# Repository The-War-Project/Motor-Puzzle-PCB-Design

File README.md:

# Motor-Puzzle-PCB-Design
 PCB Design in Kicad of the Motor Puzzle

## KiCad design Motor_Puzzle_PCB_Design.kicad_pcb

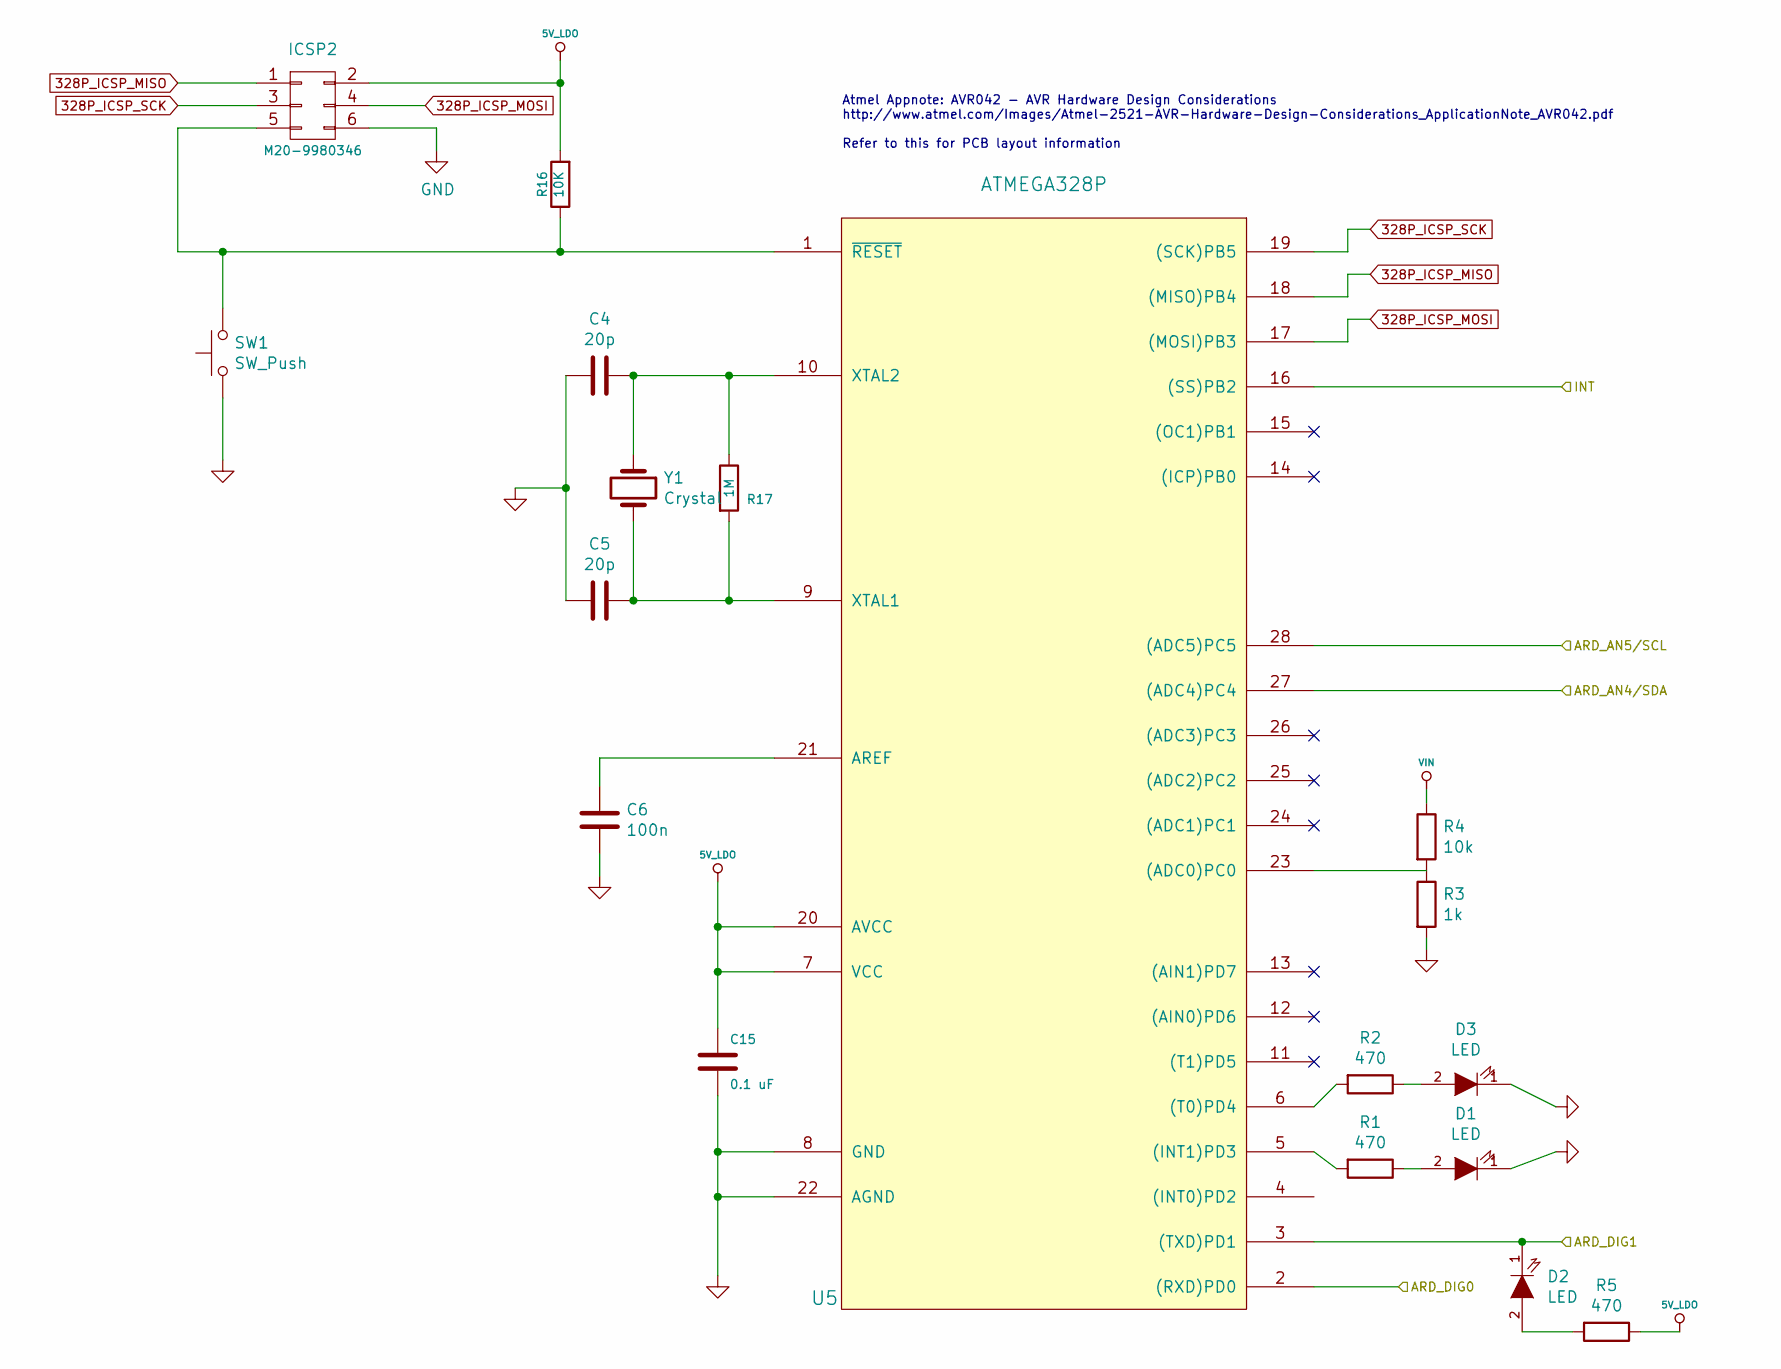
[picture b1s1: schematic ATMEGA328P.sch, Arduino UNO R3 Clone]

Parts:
C4, C5: 20p; C_0805_2012Metric_Pad1.15x1.40mm_HandSolder
C6: 100n; C_0805_2012Metric_Pad1.15x1.40mm_HandSolder
C15: 0.1 uF; C_0805_2012Metric_Pad1.15x1.40mm_HandSolder
D1, D2, D3: LED; LED_0805_2012Metric_Pad1.15x1.40mm_HandSolder
ICSP2: M20-9980346; PinSocket_2x03_P2.54mm_Vertical
R1, R2, R5: 470; R_0805_2012Metric_Pad1.15x1.40mm_HandSolder
R3: 1k; R_0805_2012Metric_Pad1.15x1.40mm_HandSolder
R4: 10k; R_0805_2012Metric_Pad1.15x1.40mm_HandSolder
R16: 10K; R_0805_2012Metric_Pad1.15x1.40mm_HandSolder
R17: 1M; R_0805_2012Metric_Pad1.15x1.40mm_HandSolder
SW1: SW_Push; SW_PUSH_6mm_H7.3mm
U5: ATMEGA328P; QFP80P900X900X120-32N
Y1: Crystal; Crystal_SMD_7050-2Pin_7.0x5.0mm_HandSoldering

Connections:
5V_LDO: C15.1, ICSP2.2, R5.1, R16.2, U5.7 (VCC), U5.20 (AVCC); also elsewhere on the board
328P_ICSP_MISO: ICSP2.1, U5.18 ((MISO)PB4)
328P_ICSP_MOSI: ICSP2.4, U5.17 ((MOSI)PB3)
328P_ICSP_SCK: ICSP2.3, U5.19 ((SCK)PB5)
/ATMEGA328P/ARD_AN4/SDA: U5.27 ((ADC4)PC4); also elsewhere on the board
/ATMEGA328P/ARD_AN5/SCL: U5.28 ((ADC5)PC5); also elsewhere on the board
/ATMEGA328P/ARD_DIG0: U5.2 ((RXD)PD0); also elsewhere on the board
/ATMEGA328P/ARD_DIG1: D2.1 (K), U5.3 ((TXD)PD1); also elsewhere on the board
/ATMEGA328P/INT: U5.16 ((SS)PB2); also elsewhere on the board
GND: C4.2, C5.2, C6.2, C15.2, D1.1 (K), D3.1 (K), ICSP2.6, R3.2, SW1.1, U5.8 (GND), U5.22 (AGND); also elsewhere on the board
unnamed: C4.1, R17.1, U5.10 (XTAL2), Y1.1
unnamed: C5.1, R17.2, U5.9 (XTAL1), Y1.2
unnamed: C6.1, U5.21 (AREF)
unnamed: D1.2 (A), R1.1
unnamed: D2.2 (A), R5.2
unnamed: D3.2 (A), R2.1
unnamed: ICSP2.5, R16.1, SW1.2, U5.1 (~RESET)
unnamed: R3.1, R4.2, U5.23 ((ADC0)PC0)
Vin: R4.1; also elsewhere on the board

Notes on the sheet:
Atmel Appnote: AVR042 - AVR Hardware Design Considerations http://www.atmel.com/Images/Atmel-2521-AVR-Hardware-Design-Considerations_ApplicationNote_AVR042.pdf Refer to this for PCB layout information

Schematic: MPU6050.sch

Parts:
C2: 100n
C3: 2.2n
R1, R2: 2.2k

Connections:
5V_LDO: C2.1, C3.1; also elsewhere on the board
GND: C2.2, C3.2; also elsewhere on the board
unnamed 13: R1.1; also elsewhere on the board
unnamed 15: R2.1; also elsewhere on the board

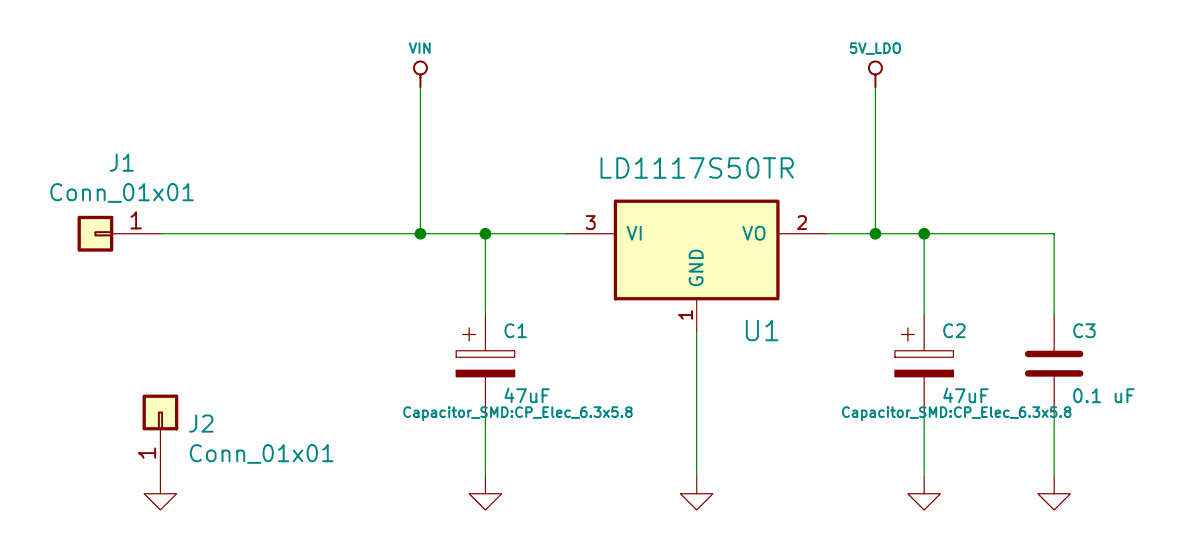
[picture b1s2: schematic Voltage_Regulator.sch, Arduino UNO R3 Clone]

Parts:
C1, C2: 47uF; CP_Elec_6.3x5.8
C3: 0.1 uF; C_0805_2012Metric_Pad1.15x1.40mm_HandSolder
J1, J2: Conn_01x01; SolderWirePad_1x01_SMD_5x10mm
U1: LD1117S50TR; SOT223

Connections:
5V_LDO: C2.1, C3.1, U1.2 (VO); also elsewhere on the board
GND: C1.2, C2.2, C3.2, J2.1, U1.1 (GND); also elsewhere on the board
Vin: C1.1, J1.1, U1.3 (VI); also elsewhere on the board

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
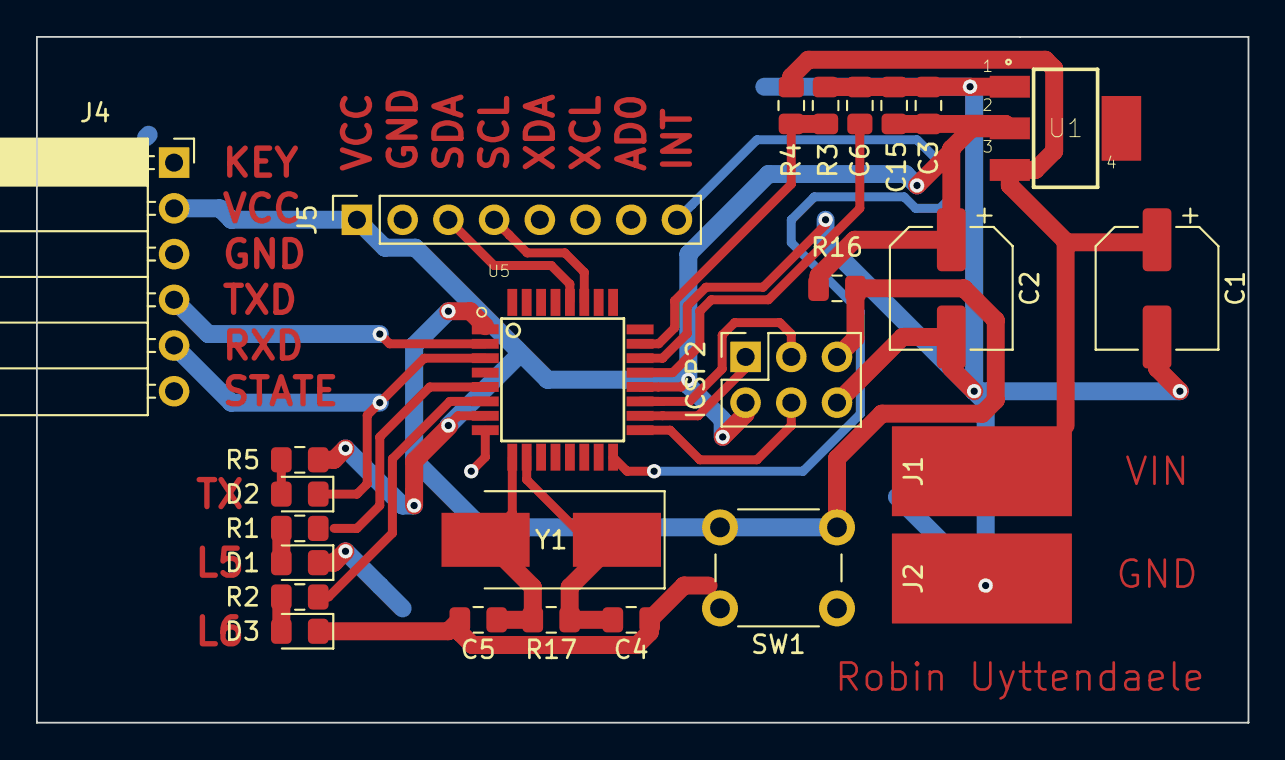
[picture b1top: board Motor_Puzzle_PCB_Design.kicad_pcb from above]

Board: 2 copper layers, 67.3 x 38.1 mm, 26 parts (0 on the bottom side), 21 nets.

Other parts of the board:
J4: Conn_01x06; PinSocket_1x06_P2.54mm_Horizontal
J5: Conn_01x08; PinSocket_1x08_P2.54mm_Vertical

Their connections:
5V_LDO: J4.2, J5.1; also elsewhere on the board
/ATMEGA328P/ARD_AN4/SDA: J5.4; also elsewhere on the board
/ATMEGA328P/ARD_AN5/SCL: J5.3; also elsewhere on the board
/ATMEGA328P/ARD_DIG0: J4.4; also elsewhere on the board
/ATMEGA328P/ARD_DIG1: J4.5; also elsewhere on the board
/ATMEGA328P/INT: J5.8; also elsewhere on the board
GND: J4.3, J5.2, J5.7; also elsewhere on the board
